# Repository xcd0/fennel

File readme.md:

# fennel
T
fan90のPCB、アクリルケースの発注が終わった。暇。この間に次のキーボードを作る。  
とりあえず名前はそのまま引き継ぐ。古いものは別ブランチに残す。別リポジトリにするかも...

## コンセプト

両手用左右分離型キーボード。fan90を小さくした。 片手に37キーの予定。  
ただしキーマトリクスが余る分を小さなリセットスイッチなどで設け、  
あまり使用頻度が高くない機能を割り当てる(マイコンの設定など)。  

* 指に合わせていい感じにキーが配置されてる両手で使えるキーボード欲しい。fan90二つはちょっと...
* fan90は流行に逆らったマキシマムな設計だったので、次は長いものに巻かれる小さ目な設計にする。
* 基盤はfan90と同じように両面対応する。
* fan90では筋力的にできなかった左右分割のキーボードにする。（左右間で通信する）
* ~~ケースはできれば3Dプリンターを使ってみる。~~ 基盤でケース作る方向にした。
* fan90のねじ数が少なくてちょっとたわむのでねじを増やす。
* Pro MicroではなくBluePillを使ってみる。

外形が難しい... \_(:3 」∠ )\_

## 設計

fan90に比べ、
* 左右分離(通信)
* BluePillを使う(ARM)
の2点により難易度が上昇している。
というか参考にできる情報がすくない。

現状回路がよくなさそうなので長い目で決めていく。

* UART半二重通信をする予定
	* 
	* 右手のbluepillはスキャンしてひたすら左手に送信するだけ
	* 左手は受け取って左手のスキャン情報と合わせてPCにUSB経由で送信
	* 通信用の信号線(回路図のdata)はpullupしつつ、GNDとツェナーダイオードでつなぐ。
* pullup抵抗を入れる
	* 10kΩが多いみたい。
	* 1.5kΩの抵抗が余ってるからこれでもいいかな...
	* wikipediaによるとバイポーラは1kΩ～4.7kΩ、CMOSでは220kΩ～1MΩらしい
	* データシートにweak pull-up equivalent resistorの記述があるので、  
	内蔵のプルアップ抵抗も使えるみたい。VINとVSSをつなぐと30～50kΩになるみたい。(43ページ)
* RX は入力端子なので保護抵抗を入れる。
	* これも1.5kΩでいいかな...
	* データシートにたしかに10kΩ書いてあるので10kΩにした方がよさそう
* 使ってないIOピンもVCCかGNDに10kΩ挟んでつなぐ
	* どっちでもいいみたい
	* これは外部でプルアップ/ダウンする必要があるみたい
	> All unused pins must be held at a fixed voltage, by using the I/O output mode, an external pull-up or pull-down resistor
* キーマトリクスに割り当てるピン配置を変える

* 異種面付けをしてみた
	
	* お値段 5枚製造
		* 異種面付けで基板製造の費用$93
		* 異種面付けしないで３枚頼んだ時の基板製造費$33
	* かすかに安いが、後加工が必要になるので、その点で普通に注文したほうよい。

### STM32F103について

調べて分かったことのメモ。間違っているかも。

* 内部回路の電源が分かれている。
	* VBAT はRTCとか用
		* ボタン電池とかをつないでRTCを維持できるみたい。
	* 1.8Vはコア回路用
	* VDDはデジタル回路用
	* VDDAはアナログ回路用

* リセットは3種類ある
	1. 電源を切る
	1. NRSTをGNDにつなぐ
	1. backup領域のみリセットする(そもそもbackup領域とは..)
		* BDRSTレジスタでリセット
		* VDDがONでリセット
		* VBATがONでリセット

* ピンについて
	* PA9がTx、PA10がRx。
	* PA15、PB3、PB4はJRAGデバッグに使われている(JTAGデバッグとは...)ので使おうとするとひと手間いる。
	* PB2はジャンパにつながっている。
	* PA11、PA12はUSB端子につながっている。
	* generic bootloader向け
		* bootloaderの種類はbluepillの実装に合わせる。generic_boot20_xxx.binのxxxはLEDのpinに合わせる。
			* 合わせることでDFUモードの状態をLEDで表示できる。
		* PA12はUSBリセットに使われているので、外部HWをつながない方がよい。
		* PC13はDFUの状態をLEDで表示するのに使われているので、外部HWをつながない方がよい。
		* PC14はNRSTに使われているので、外部HWをつながない方がよい。
			* PC14を3.3VにプルアップするとDFU永続モードになる？
			* DFU永続モードにできるなら有用なので専用回路を実装したい。
			* PC14をhigh→リセット→書き込み→PC14を開放→リセットの流れっぽい。

* 書き込みについて
	* USB経由での書き込みはタイミングよくリセットボタンを押す必要があるらしい。
		* 「Arduinoの書き込みを押した後0.5秒後くらいにボードのリセットを押す」らしい...

## リンク集

* 一番詳しかった  
ＤＥＫＯのアヤシいお部屋。 - STM32F103 https://ht-deko.com/arduino/stm32f103c8t6.html

* DFUモードの0.5秒の情報はここ  
adfmac/bluepill-arduino.md https://gist.github.com/tadfmac/f1dffc8c674ddaa8bd2340a8ddec65be

## ケース

基板と一緒に頼んだ。

## 回路間違っていた。
頼んだタイミングが残業で疲れた深夜だったため、いろいろミスった状態で発注した\_(:3 」∠ )\_
労働は体に良くない。

とりあえずゴリゴリ基盤を削って空中配線してごまかした。

## ファームウェア

[Ortho 75](https://github.com/qmk/qmk_firmware/tree/master/keyboards/cannonkeys/ortho75)を参考にする。

とりあえずこぴっていじる

<!--{{{-->

## 以下古いバージョン

<details>
<summary>v1 fan90 片手用フルキーボード</summary>

## one hand keyboard fan90

片手用キーボードです。G13のような用途を想定しています。  
左手で使うことを想定していますが、右手でも使えるようにPCBは作っています。  
流行りのミニマムなキーボードとは反対方向のマキシマムな方向のキーボードです。  
両手で使うことを想定していませんが、両面対応しているので2つ用意すれば可能です。  

初めての自作キーボードなので楽しみなのと不安なのが混在しています\_(:3 」∠ )\_
あくまで初めてつくる自作キーボードであるため、当然ながら動かない可能性が高いです。

<details>
<summary>開発経緯</summary>

### キーボード割ろうとしたら曲がった
* ありものは素晴らしい、でも自分で作ってみたい。よし、初めてのキーボード自作だ！PCBから作るぞ\\('ω')/
* 今使ってるhelixよい。でもErgodox的な縦のずれがあるキーボードもよさそう。そういうの作ろう...
* 左右分割型のキーボード良い。割りたい！でも左右の通信とかどうやってるんだろう...ちゃんと作れるかな...
* とりあえずキーを並べてみる。小指とか根元に近く配置しよう...
* 見た目汚いな...とりあえずきれいに並べてみるか...あれ、なんか曲がってきた...
* あれこれ片手でフルキーボードいけるんじゃ...

という感じでした\_(:3 」∠ )\_  
つまりキーボードを割ろうとしたが、  
筋力が足りなかったため（左右に分割したときの左右間の通信を電源(VCC,GND)と信号線の3本でどうやって通信してるのかわからなかったので）、  
割れずに曲がってしまった。  
次作るときは割りたい。  
名前は見た目がうちわのようになったため。  もちろん余った基板は重めの団扇として使うことができる。
鍋敷きにしてもよい。
</details>

<details>
<summary>構想</summary>

#### コンセプト
以下で東西南北を言うときは、左手で中指の方向を北とした場合の手のひらからの方向を指します。

* 片手でたくさんのキーを使える。
	* フルキーボード相当のキーを使えるものとする。
		* 現状6x15のマトリクスで87キーを配置。
		* 残り３キーはあまり使わない用途向けにリセットスイッチ部品で配置。

* 片手で使いやすい。
	* 指毎の特徴に合わせて配置する。  
		例えば
		* 親指はゲームのコントローラーで多用されるように本来非常に性能が良い。  
		しかしキーボードを使う上で親指を生かすのは難しい。  
		Twitterの投票によると親指に複数のキーを割り当てているときに使っているキーの数はせいぜい4キーらしい。  
		このキーボードでは多めに5キーを割り当てる。
		* 人差し指は性能が良くQWERTYでもほかの指より多いキーを担当する。  
		このキーボードでも人差し指の担当は多くする。
		* 中指は人差し指と同じくらいのせいのがある。中指にも多めのキーを割り当てる。
		* 薬指は中指と一緒に動かないと性能が良くないので、キーボードではあまり性能を発揮できない。
		ただし、北西方向は強く、北西方向に関しては小指より適している。。
		* 小指は短いので、北西方向の移動は難しい。  
		しかし西方向、南西方向はそこそこ性能が良い。
	* 指に合わせてキーを配置する。
		* 変則的な配置なので指１本に対して割り当てられたキーの数は様々。
			* 現状小指20、薬指15、中指12、人差し指31、親指5キー。人差し指と小指は無駄キーを含む。足しても90にはならない。
		* 将来的にはキーを立体的に配置するのもよいが、現状は平面に配置。
	* 指は伸ばした状態のほうが押しやすく、キーを押し分けやすい。
		* 指の根本に近いキーよりも指を伸ばしたときに押すキーのほうが押しやすい。
		* 指の根元に近いキーを減らし、指を伸ばしたときに押すキーを増やす。
	* レイヤーは極力つかわない。
		* シフトキーのように押しながら操作することは片手だと難しい。

* すべてのキーを常に使うキーにはせず、使う用途に合わせてカスタマイズできるよう、無駄にキーを配置する。

#### 実現方法

* 以下の2点からキーを扇状に配置する。
	* 小指の性能を発揮できるように小指のキーは手首側に寄せる。
	* 伸ばした状態で使える人差し指、中指のキーを増やす。
* 列方向には揃えず、行方向にはそろえる。
* 無駄にキーを小指の西側、人差し指の東側、すべての指の北側に配置する。つまり一回り大きくする。

#### 将来的にやりたいこと

* QMKを使わずに作る。(現状使う)
* C以外の言語で作る。(現状C言語)
* マイコンを複数種類使えるようにする。(現状むずかしい)
* raspberry pi zeroと画面を搭載して、それ単体でPCとして動作させ多機能にする。(現状ソケットのみ用意)
* ケースを3Dプリンターなどでつくる。
* キーを立体的に配置する。

</details>

### PCB設計

kicadを使って設計した。

回路は6x15のマトリクス。column方向からスキャンし、rowを検出する。  
column方向のスキャンは床に転がっていたSN74HC595を使う。  
シフトレジスタを使えば簡単にスキャンできそう。  
これで信号線数を15-5で10本減らせることになる。  
pro microはデジタルIOピンが14本、デジタルとしても使えるアナログIOピンが4本なので、
最大18本をデジタルIOとして使うことができる。
6本をrowのデジタル入力に、5本をシフトレジスタへのデジタル出力に、
2本をリセットスイッチに使用することにした。
配置は特にこだわりなく並べた。このせいで後々苦労するかもしれないがまあ初めてなので良しとする。

### アクリルケース設計

* ケースもとりあえずアクリルで作ることにした。
* ケースもDXFで入稿できるみたいなのでkicadでそのまま作った。
	* SVGでもよさそうだがそもそもSVGで線幅を狭くするとinkscapeやchromeで表示したとき線が描画されない問題があった。
* アクリルは[工房Emerge+](https://www.emergeplus.jp/laser-cutting-service/)を使ってみることにした。
	* elecrowはウェブサイトの調子が良くないのか、そもそもサービス中止中なのか、  
	https://twitter.com/xcd0/status/1233658167684296704  
	のようにfalseとなっていた。
	* 遊舎工房は、キーボードのサイズが大きいので元のアクリル板が最低でもA3より大きな必要があり、  
	A5,A4,450 X 300と、450x300以外の選択肢がなく、このサイズでも2枚発注する必要がある。  
	そして150x300程度の余白ができてしまう。
	* Emarge+は600x300に対応しており、これだと１枚に収まる。なのでここにしてみた。
	* 遊舎工房とEmerge+はillustratorありきの体制で、すごくストレスフルであった。
	* inkscapeは線幅の問題で使えず、外形と内形を色を変えるとかレイヤーを変えるとか言った操作はillustratorがないと難しいというか不可能な作業であった。
	* 今回５個ほどソフトを試したが、どれも満たせずあきらめてillustratorの7日間仕様版を使った。
	* 次回はaiやsvgではなくDXFで入稿したい。
	* elecrow復活してほしい...
* データ蹴られるかと思ったがとりあえず通った。
* DXFもレイヤー分けていればよいらしい。

### プログラム作成

qmkでもよいがとりあえず動作確認にarduinoを使う。
以下を参考にarduino studioで書き込めるか調べる。
https://learn.sparkfun.com/tutorials/pro-micro--fio-v3-hookup-guide#installing-windows
https://learn.sparkfun.com/tutorials/pro-micro--fio-v3-hookup-guide/hardware-overview-pro-micro

</details>
<!--}}}-->

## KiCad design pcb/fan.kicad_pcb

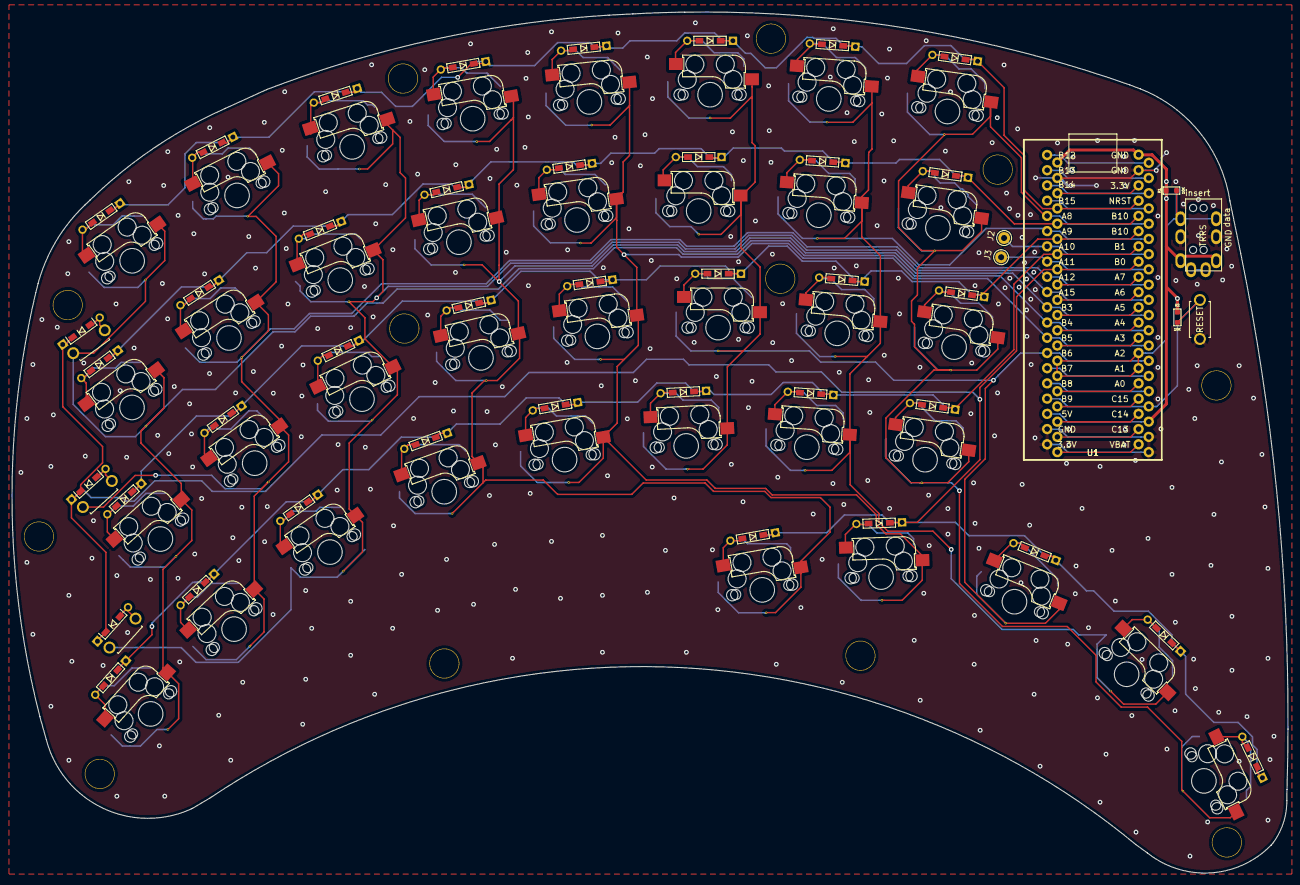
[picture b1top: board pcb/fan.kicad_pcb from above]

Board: 2 copper layers, 212.8 x 143.6 mm, 59 parts (0 on the bottom side), 19 nets.

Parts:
J1: MJ-4PP-9
J2, J3: Conn_01x01_Female; Pin_D1.0mm_L10.0mm
R1, R2: 10K; R_1608_rev2
Ref**: Val**; HOLE
Ref**#2, Ref**#3, Ref**#4, Ref**#5, Ref**#6, Ref**#7, Ref**#8, Ref**#9, Ref**#10, Ref**#11, Ref**#12: Val**; HOLE
SW1, SW2, SW3, SW4, SW6, SW7, SW8, SW9, SW11, SW12, SW13, SW14, SW16, SW17, SW18, SW19, SW20, SW21, SW22, SW23, SW24, SW25, SW26, SW27, SW28, SW29, SW30, SW31, SW32, SW33, SW34, SW35, SW36, SW37, SW38, SW39, SW40: SW_PUSH-kbd; CherryMX_MidHeight_Hotswap_edit
SW5, SW10, SW15: SW_PUSH-kbd; ResetSW_with_diode
SW41: SW_PUSH; ResetSW
U1: BluePill_STM32F103C; BluePill_STM32F103C_0.9_Double

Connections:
GND: J1.C, SW41.2, U1.19, U1.20, U1.39
unnamed: J2.1, U1.7
unnamed: J3.1, U1.8
Rx: J1.B, R1.2, U1.26, U1.27
VCC: J1.D, R1.1, R2.1, U1.18, U1.40
col00: SW1.1, SW2.1, SW3.1, SW4.1, SW5.1, U1.12
col01: SW6.1, SW7.1, SW8.1, SW9.1, SW10.1, U1.9
col02: SW11.1, SW12.1, SW13.1, SW14.1, SW15.1, U1.10
col03: SW16.1, SW17.1, SW18.1, SW19.1, SW20.1, U1.11
col04: SW21.1, SW22.1, SW23.1, SW24.1, SW25.1, U1.13
col05: SW26.1, SW27.1, SW28.1, SW29.1, SW30.1, U1.14
col06: SW31.1, SW32.1, SW33.1, SW34.1, SW35.1, U1.6
col07: SW36.1, SW37.1, SW38.1, SW39.1, SW40.1, U1.5
hardware_reset: R2.2, SW41.1, U1.17
row00: SW1.3, SW6.3, SW11.3, SW16.3, SW21.3, SW26.3, SW31.3, SW36.3, U1.37
row01: SW2.3, SW7.3, SW12.3, SW17.3, SW22.3, SW27.3, SW32.3, SW37.3, U1.36
row02: SW3.3, SW8.3, SW13.3, SW18.3, SW23.3, SW28.3, SW33.3, SW38.3, U1.35
row03: SW4.3, SW9.3, SW14.3, SW19.3, SW24.3, SW29.3, SW34.3, SW39.3, U1.34
row04: SW5.3, SW10.3, SW15.3, SW20.3, SW25.3, SW30.3, SW35.3, SW40.3, U1.33

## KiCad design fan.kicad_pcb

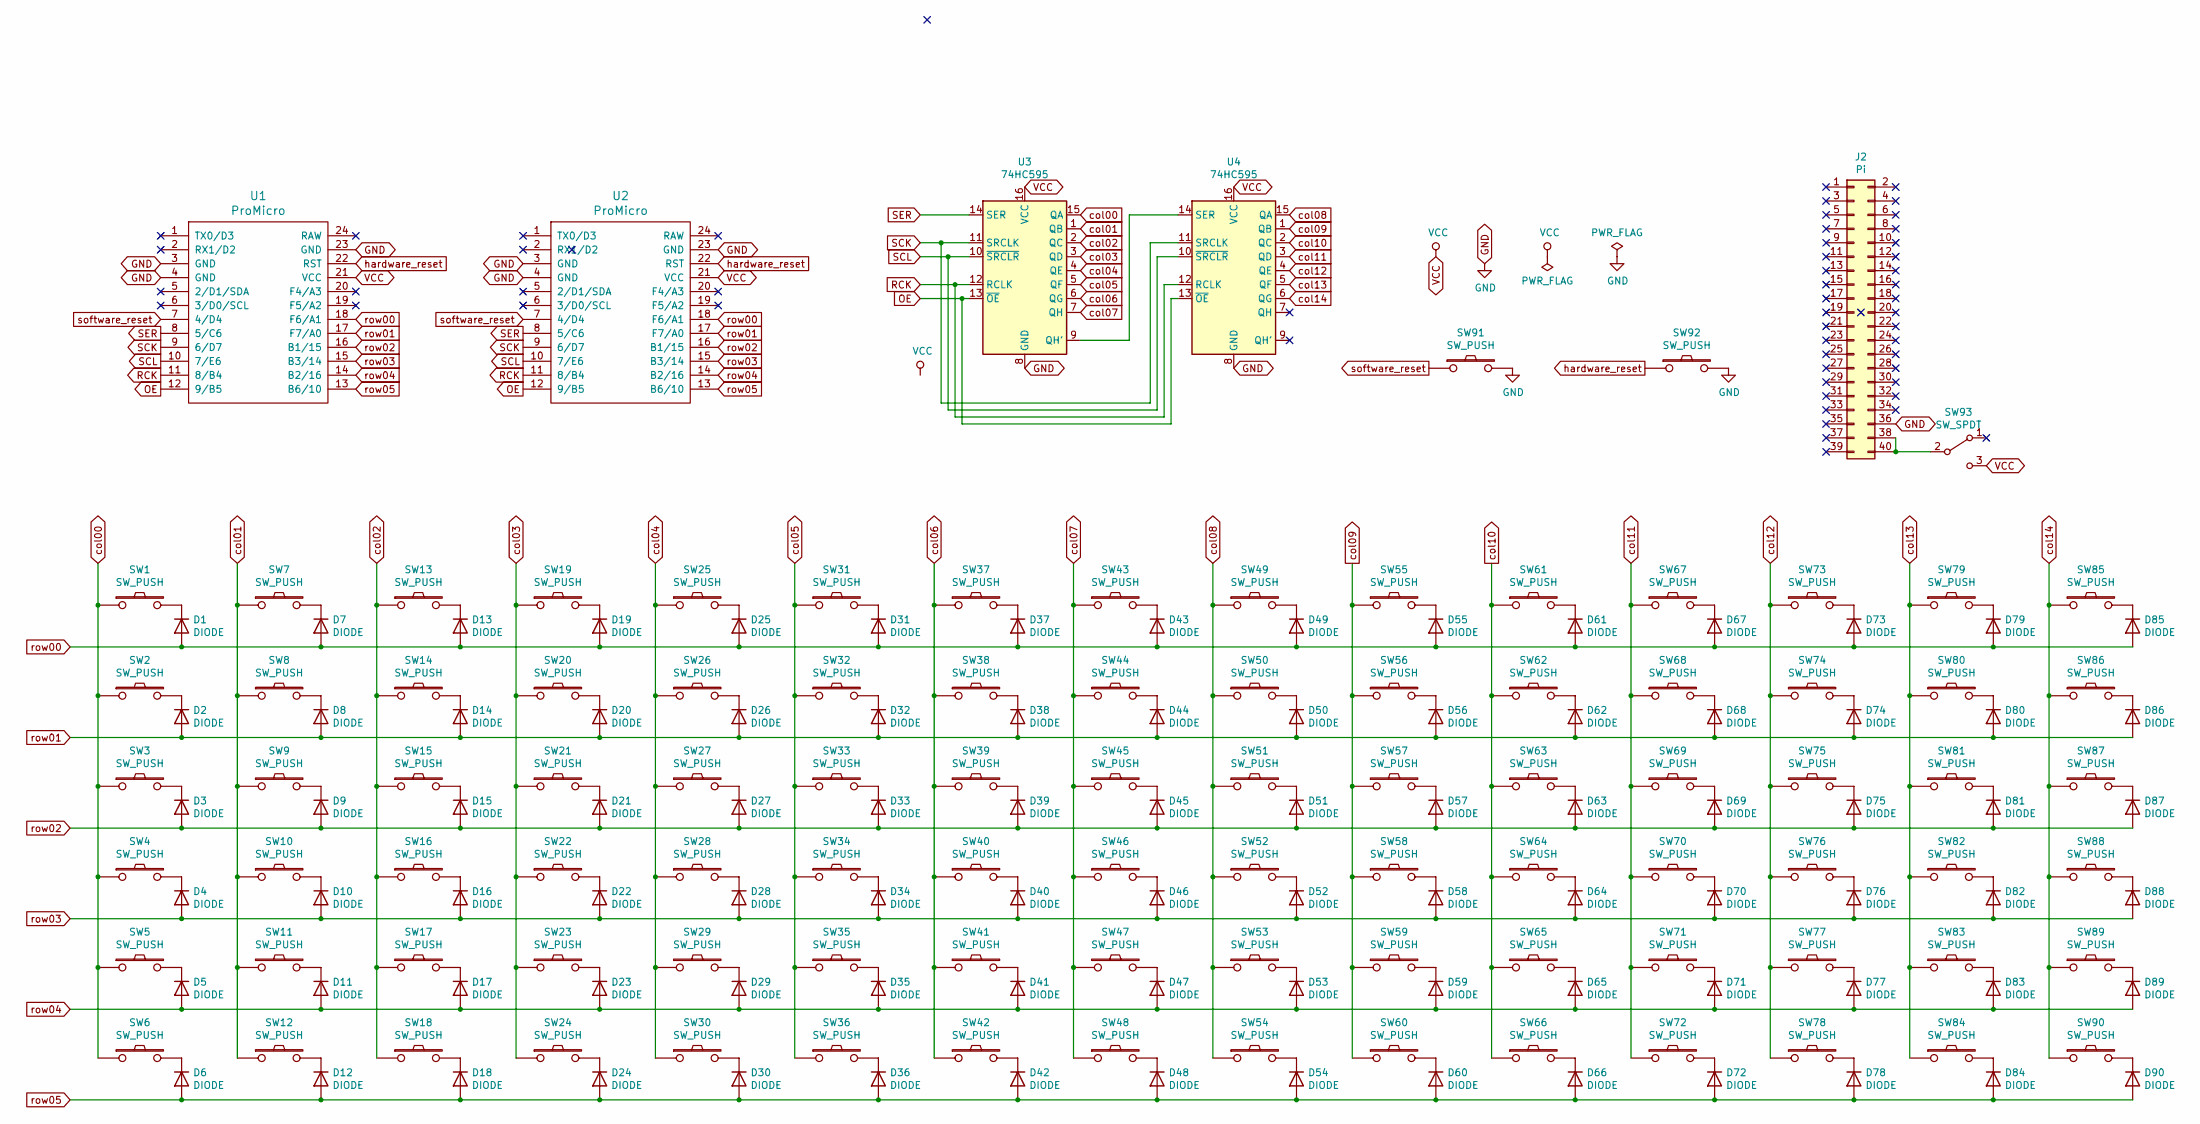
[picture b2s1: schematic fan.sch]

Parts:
D1, D2, D3, D4, D5, D6, D7, D8, D9, D10, D11, D12, D13, D14, D15, D16, D17, D18, D19, D20, D21, D22, D23, D24, D25, D26, D27, D28, D29, D30, D31, D32, D33, D34, D35, D36, D37, D38, D39, D40, D41, D42, D43, D44, D45, D46, D47, D48, D49, D50, D51, D52, D53, D54, D55, D56, D57, D58, D59, D60, D61, D62, D63, D64, D65, D66, D67, D68, D69, D70, D71, D72, D73, D74, D75, D76, D77, D78, D79, D80, D81, D82, D83, D84, D85, D86, D87, D88, D89, D90: DIODE; D3_TH_SMD
J2: Pi; PinSocket_2x20_P2.54mm_Vertical
SW1, SW2, SW3, SW4, SW5, SW6, SW7, SW8, SW9, SW10, SW11, SW12, SW13, SW14, SW15, SW16, SW17, SW18, SW19, SW20, SW21, SW22, SW23, SW24, SW25, SW26, SW27, SW28, SW29, SW30, SW31, SW32, SW33, SW34, SW35, SW36, SW37, SW38, SW39, SW40, SW41, SW42, SW43, SW44, SW45, SW46, SW47, SW48, SW51, SW52, SW53, SW54, SW56, SW57, SW58, SW59, SW60, SW61, SW62, SW63, SW64, SW65, SW66, SW67, SW68, SW69, SW70, SW71, SW72, SW73, SW74, SW75, SW76, SW77, SW78, SW79, SW80, SW81, SW82, SW83, SW84, SW85, SW86, SW87, SW88, SW89, SW90: SW_PUSH; CherryMX_Hotswap
SW49, SW50, SW55, SW91, SW92: SW_PUSH; ResetSW
SW93: SW_SPDT; SW_Slide_1P2T_CK_OS102011MS2Q
U1, U2: ProMicro; ProMicro_v3.5
U3, U4: 74HC595; DIP-16_W7.62mm

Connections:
GND: J2.36, SW91.2, SW92.2, U1.3 (GND), U1.4 (GND), U1.23 (GND), U2.3 (GND), U2.4 (GND), U2.23 (GND), U3.8 (GND), U4.8 (GND)
unnamed: D1.2 (K), SW1.2
unnamed: D2.2 (K), SW2.2
unnamed: D3.2 (K), SW3.2
unnamed: D4.2 (K), SW4.2
unnamed: D5.2 (K), SW5.2
unnamed: D6.2 (K), SW6.2
unnamed: D7.2 (K), SW7.2
unnamed: D8.2 (K), SW8.2
unnamed: D9.2 (K), SW9.2
unnamed: D10.2 (K), SW10.2
unnamed: D11.2 (K), SW11.2
unnamed: D12.2 (K), SW12.2
unnamed: D13.2 (K), SW13.2
unnamed: D14.2 (K), SW14.2
unnamed: D15.2 (K), SW15.2
unnamed: D16.2 (K), SW16.2
unnamed: D17.2 (K), SW17.2
unnamed: D18.2 (K), SW18.2
unnamed: D19.2 (K), SW19.2
unnamed: D20.2 (K), SW20.2
unnamed: D21.2 (K), SW21.2
unnamed: D22.2 (K), SW22.2
unnamed: D23.2 (K), SW23.2
unnamed: D24.2 (K), SW24.2
unnamed: D25.2 (K), SW25.2
unnamed: D26.2 (K), SW26.2
unnamed: D27.2 (K), SW27.2
unnamed: D28.2 (K), SW28.2
unnamed: D29.2 (K), SW29.2
unnamed: D30.2 (K), SW30.2
unnamed: D31.2 (K), SW31.2
unnamed: D32.2 (K), SW32.2
unnamed: D33.2 (K), SW33.2
unnamed: D34.2 (K), SW34.2
unnamed: D35.2 (K), SW35.2
unnamed: D36.2 (K), SW36.2
unnamed: D37.2 (K), SW37.2
unnamed: D38.2 (K), SW38.2
unnamed: D39.2 (K), SW39.2
unnamed: D40.2 (K), SW40.2
unnamed: D41.2 (K), SW41.2
unnamed: D42.2 (K), SW42.2
unnamed: D43.2 (K), SW43.2
unnamed: D44.2 (K), SW44.2
unnamed: D45.2 (K), SW45.2
unnamed: D46.2 (K), SW46.2
unnamed: D47.2 (K), SW47.2
unnamed: D48.2 (K), SW48.2
unnamed: D49.2 (K), SW49.2
unnamed: D50.2 (K), SW50.2
unnamed: D51.2 (K), SW51.2
unnamed: D52.2 (K), SW52.2
unnamed: D53.2 (K), SW53.2
unnamed: D54.2 (K), SW54.2
unnamed: D55.2 (K), SW55.2
unnamed: D56.2 (K), SW56.2
unnamed: D57.2 (K), SW57.2
unnamed: D58.2 (K), SW58.2
unnamed: D59.2 (K), SW59.2
unnamed: D60.2 (K), SW60.2
unnamed: D61.2 (K), SW61.2
unnamed: D62.2 (K), SW62.2
unnamed: D63.2 (K), SW63.2
unnamed: D64.2 (K), SW64.2
unnamed: D65.2 (K), SW65.2
unnamed: D66.2 (K), SW66.2
unnamed: D67.2 (K), SW67.2
unnamed: D68.2 (K), SW68.2
unnamed: D69.2 (K), SW69.2
unnamed: D70.2 (K), SW70.2
unnamed: D71.2 (K), SW71.2
unnamed: D72.2 (K), SW72.2
unnamed: D73.2 (K), SW73.2
unnamed: D74.2 (K), SW74.2
unnamed: D75.2 (K), SW75.2
unnamed: D76.2 (K), SW76.2
unnamed: D77.2 (K), SW77.2
unnamed: D78.2 (K), SW78.2
unnamed: D79.2 (K), SW79.2
unnamed: D80.2 (K), SW80.2
unnamed: D81.2 (K), SW81.2
unnamed: D82.2 (K), SW82.2
unnamed: D83.2 (K), SW83.2
unnamed: D84.2 (K), SW84.2
unnamed: D85.2 (K), SW85.2
unnamed: D86.2 (K), SW86.2
unnamed: D87.2 (K), SW87.2
unnamed: D88.2 (K), SW88.2
unnamed: D89.2 (K), SW89.2
unnamed: D90.2 (K), SW90.2
unnamed: J2.38, J2.40, SW93.2 (B)
unnamed: U3.9 (QH'), U4.14 (SER)
OE: U1.12 (9/B5), U2.12 (9/B5), U3.13 (~OE), U4.13 (~OE)
RCK: U1.11 (8/B4), U2.11 (8/B4), U3.12 (RCLK), U4.12 (RCLK)
SCK: U1.9 (6/D7), U2.9 (6/D7), U3.11 (SRCLK), U4.11 (SRCLK)
SCL: U1.10 (7/E6), U2.10 (7/E6), U3.10 (~SRCLR), U4.10 (~SRCLR)
SER: U1.8 (5/C6), U2.8 (5/C6), U3.14 (SER)
VCC: SW93.3 (C), U1.21 (VCC), U2.21 (VCC), U3.16 (VCC), U4.16 (VCC)
col00: SW1.1, SW2.1, SW3.1, SW4.1, SW5.1, SW6.1, U3.15 (QA)
col01: SW7.1, SW8.1, SW9.1, SW10.1, SW11.1, SW12.1, U3.1 (QB)
col02: SW13.1, SW14.1, SW15.1, SW16.1, SW17.1, SW18.1, U3.2 (QC)
col03: SW19.1, SW20.1, SW21.1, SW22.1, SW23.1, SW24.1, U3.3 (QD)
col04: SW25.1, SW26.1, SW27.1, SW28.1, SW29.1, SW30.1, U3.4 (QE)
col05: SW31.1, SW32.1, SW33.1, SW34.1, SW35.1, SW36.1, U3.5 (QF)
col06: SW37.1, SW38.1, SW39.1, SW40.1, SW41.1, SW42.1, U3.6 (QG)
col07: SW43.1, SW44.1, SW45.1, SW46.1, SW47.1, SW48.1, U3.7 (QH)
col08: SW49.1, SW50.1, SW51.1, SW52.1, SW53.1, SW54.1, U4.15 (QA)
col09: SW55.1, SW56.1, SW57.1, SW58.1, SW59.1, SW60.1, U4.1 (QB)
col10: SW61.1, SW62.1, SW63.1, SW64.1, SW65.1, SW66.1, U4.2 (QC)
col11: SW67.1, SW68.1, SW69.1, SW70.1, SW71.1, SW72.1, U4.3 (QD)
col12: SW73.1, SW74.1, SW75.1, SW76.1, SW77.1, SW78.1, U4.4 (QE)
col13: SW79.1, SW80.1, SW81.1, SW82.1, SW83.1, SW84.1, U4.5 (QF)
col14: SW85.1, SW86.1, SW87.1, SW88.1, SW89.1, SW90.1, U4.6 (QG)
hardware_reset: SW92.1, U1.22 (RST), U2.22 (RST)
row00: D1.1 (A), D7.1 (A), D13.1 (A), D19.1 (A), D25.1 (A), D31.1 (A), D37.1 (A), D43.1 (A), D49.1 (A), D55.1 (A), D61.1 (A), D67.1 (A), D73.1 (A), D79.1 (A), D85.1 (A), U1.18 (F6/A1), U2.18 (F6/A1)
row01: D2.1 (A), D8.1 (A), D14.1 (A), D20.1 (A), D26.1 (A), D32.1 (A), D38.1 (A), D44.1 (A), D50.1 (A), D56.1 (A), D62.1 (A), D68.1 (A), D74.1 (A), D80.1 (A), D86.1 (A), U1.17 (F7/A0), U2.17 (F7/A0)
row02: D3.1 (A), D9.1 (A), D15.1 (A), D21.1 (A), D27.1 (A), D33.1 (A), D39.1 (A), D45.1 (A), D51.1 (A), D57.1 (A), D63.1 (A), D69.1 (A), D75.1 (A), D81.1 (A), D87.1 (A), U1.16 (B1/15), U2.16 (B1/15)
row03: D4.1 (A), D10.1 (A), D16.1 (A), D22.1 (A), D28.1 (A), D34.1 (A), D40.1 (A), D46.1 (A), D52.1 (A), D58.1 (A), D64.1 (A), D70.1 (A), D76.1 (A), D82.1 (A), D88.1 (A), U1.15 (B3/14), U2.15 (B3/14)
row04: D5.1 (A), D11.1 (A), D17.1 (A), D23.1 (A), D29.1 (A), D35.1 (A), D41.1 (A), D47.1 (A), D53.1 (A), D59.1 (A), D65.1 (A), D71.1 (A), D77.1 (A), D83.1 (A), D89.1 (A), U1.14 (B2/16), U2.14 (B2/16)
row05: D6.1 (A), D12.1 (A), D18.1 (A), D24.1 (A), D30.1 (A), D36.1 (A), D42.1 (A), D48.1 (A), D54.1 (A), D60.1 (A), D66.1 (A), D72.1 (A), D78.1 (A), D84.1 (A), D90.1 (A), U1.13 (B6/10), U2.13 (B6/10)
software_reset: SW91.1, U1.7 (4/D4), U2.7 (4/D4)

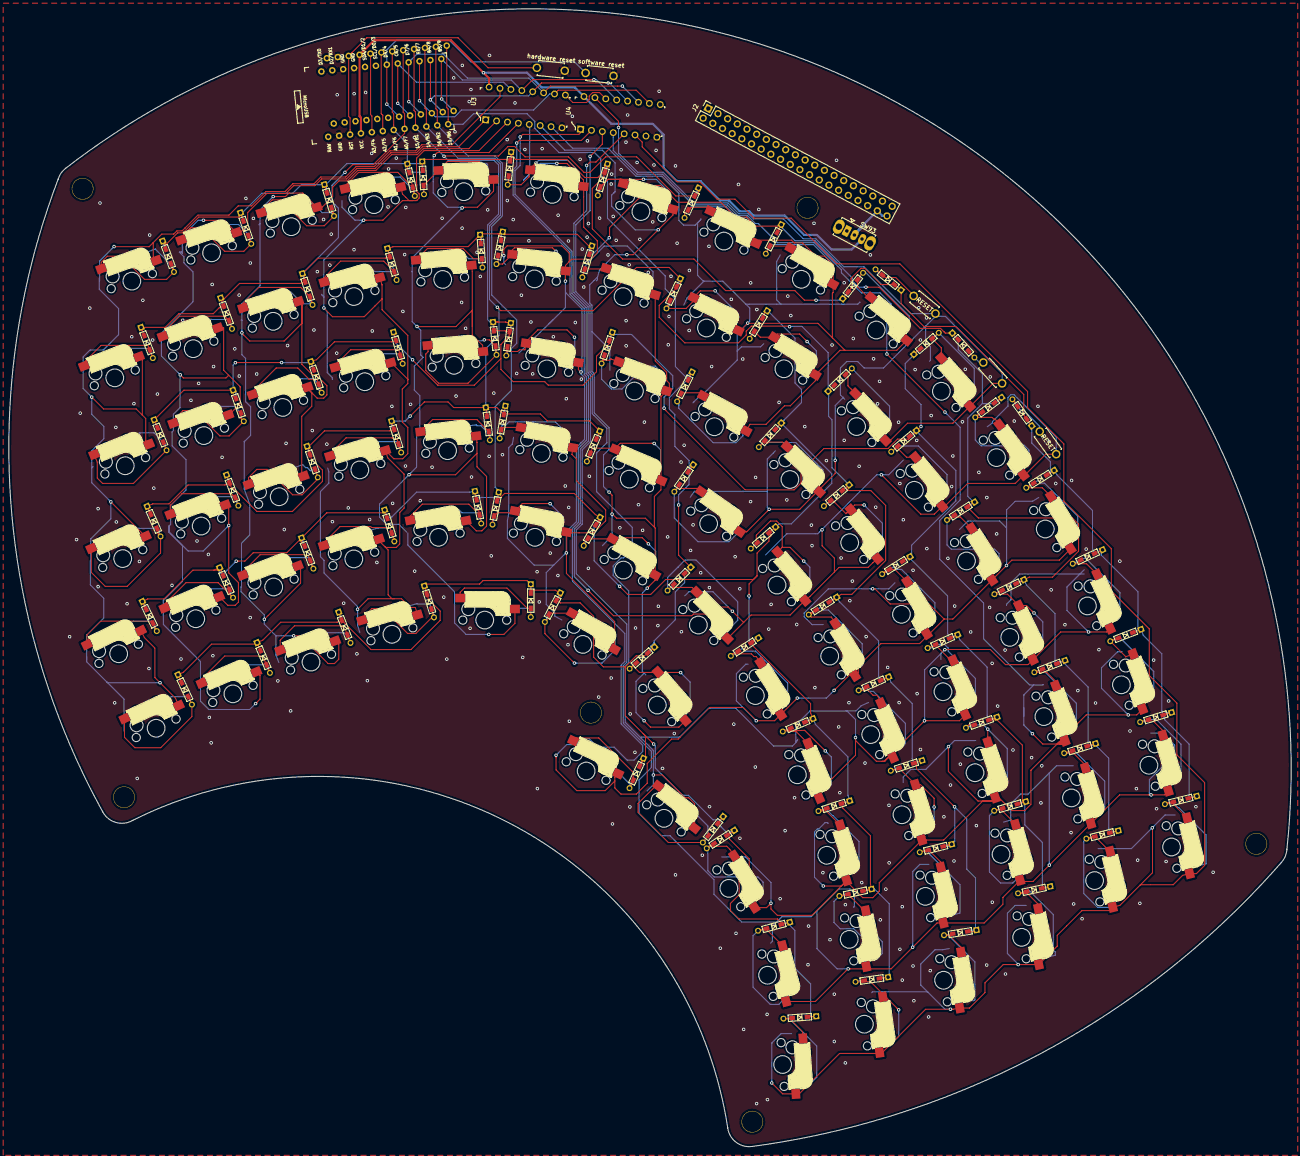
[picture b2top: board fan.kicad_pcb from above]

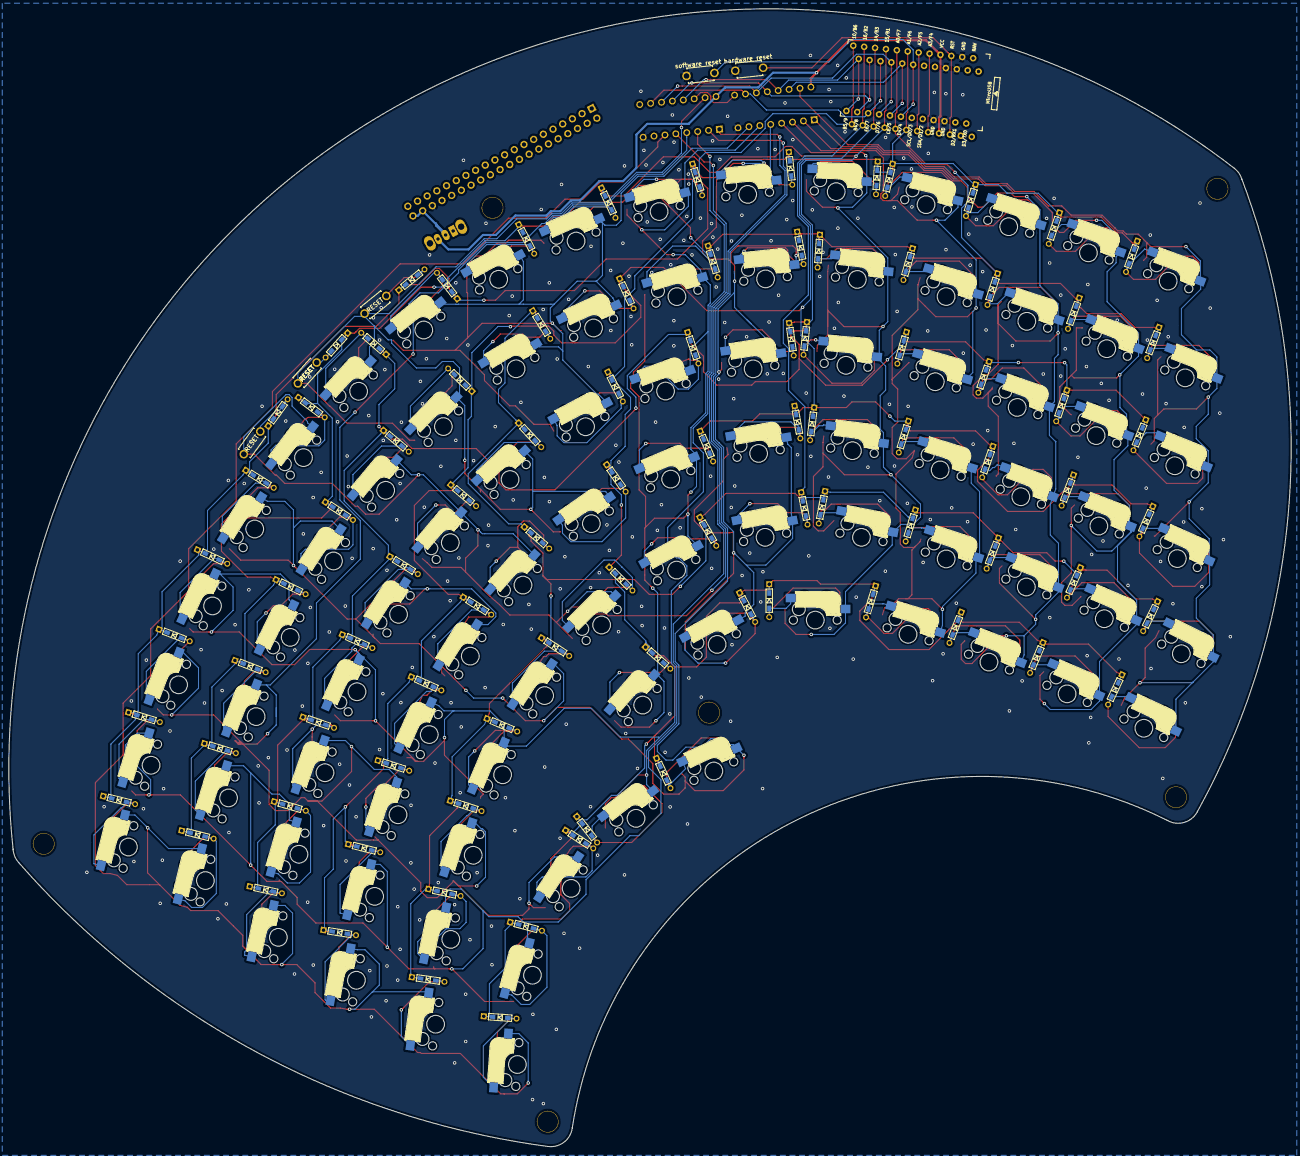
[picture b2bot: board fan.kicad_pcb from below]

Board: 2 copper layers, 297.2 x 263.7 mm, 194 parts (91 on the bottom side), 122 nets.

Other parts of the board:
Ref**: Val**; HOLE
Ref**#2, Ref**#3, Ref**#4, Ref**#5, Ref**#6: Val**; HOLE

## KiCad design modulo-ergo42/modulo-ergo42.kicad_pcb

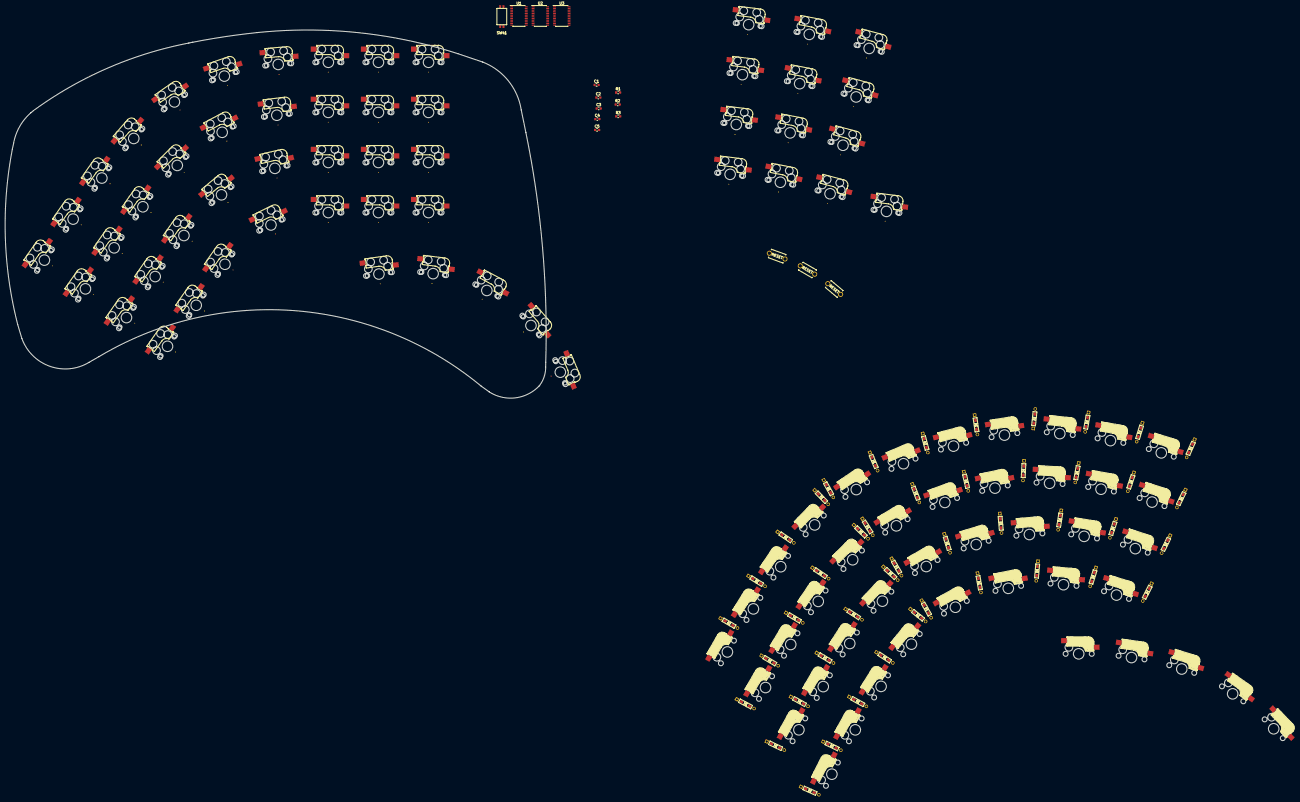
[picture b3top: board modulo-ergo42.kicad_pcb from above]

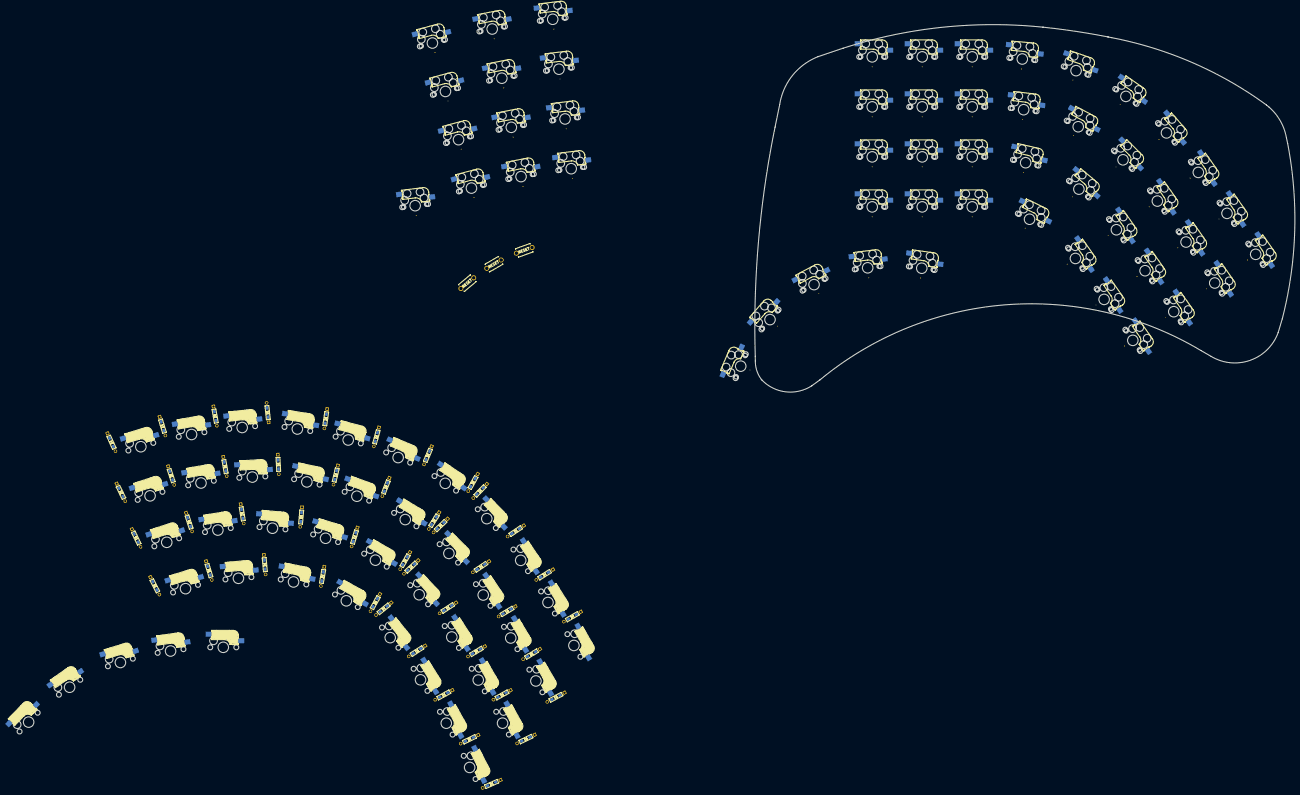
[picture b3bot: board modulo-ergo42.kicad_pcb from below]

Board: 2 copper layers, 210.6 x 143.3 mm, 155 parts (45 on the bottom side), 47 nets, no tracks yet.

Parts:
C1, C2, C5: 100 nF; C_0603_1608Metric
C3, C4: 1 uF; C_0603_1608Metric
D3, D4, D5, D8, D9, D10, D11, D14, D15, D16, D17, D20, D21, D22, D23, D26, D27, D28, D29, D32, D33, D34, D35, D38, D39, D40, D41, D46, D47, D48, D52, D53, D54, D57, D58, D59, D60, D62, D63, D64, D65, D68, D69, D70, D71: DIODE; D3_TH_SMD
R1: 10 kΩ; R_0603_1608Metric
R2, R3: 1 MΩ; R_0603_1608Metric
SW1, SW1#2, SW2, SW2#2, SW3, SW3#2, SW4, SW4#2, SW5, SW6, SW7, SW7#2, SW8, SW8#2, SW8#3, SW8#5, SW9, SW9#3, SW10#2, SW11#2, SW12, SW13, SW13#2, SW13#3, SW13#4, SW14, SW14#2, SW14#3, SW14#5, SW15#2, SW16#2, SW17#2, SW18, SW19, SW20#2, SW21#2, SW22#2, SW23#2, SW24, SW25, SW26#2, SW27#2, SW28#2, SW29#2, SW31, SW32#2, SW33#2, SW34#2, SW36, SW37, SW38#2, SW39#2: SW_Push; CherryMX_MidHeight_Hotswap_edit_without_diode
SW8#4, SW9#2, SW10, SW11, SW14#4, SW15, SW16, SW17, SW20, SW21, SW22, SW23, SW26, SW27, SW28, SW29, SW32, SW33, SW34, SW35, SW38, SW39, SW40, SW41, SW46, SW47, SW48, SW52, SW53, SW54, SW57, SW58, SW59, SW60, SW62, SW63, SW64, SW65, SW66, SW72, SW78, SW84, SW90: SW_PUSH; CherryMX_Hotswap
SW30, SW35#2, SW40#2: SW_Push; ResetSW
SW41#2: SW_DIP_x02; DipSwitch
U1, U2, U3: TCA9555PWR; TSSOP-24_4.4x7.8mm_P0.65mm

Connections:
3V3: C1.1, C2.1, C3.1, C4.1, C5.1, R1.1, R2.2, R3.1, U1.24, U2.21, U2.24, U3.21, U3.24
A1: R2.1, SW41#2.2, U1.2, U2.2, U3.2
A2: R3.2, SW41#2.1, U1.3, U2.3, U3.3
GND: C1.2, C2.2, C3.2, C4.2, C5.2, SW1#2.1, SW2#2.1, SW3#2.1, SW4#2.1, SW5.1, SW6.1, SW7#2.1, SW8#5.1, SW9#3.1, SW10#2.1, SW11#2.1, SW12.1, SW13#4.1, SW14#5.1, SW15#2.1, SW16#2.1, SW17#2.1, SW18.1, SW19.1, SW20#2.1, SW21#2.1, SW22#2.1, SW23#2.1, SW24.1, SW25.1, SW26#2.1, SW27#2.1, SW28#2.1, SW29#2.1, SW30.1, SW31.1, SW32#2.1, SW33#2.1, SW34#2.1, SW35#2.1, SW36.1, SW37.1, SW38#2.1, SW39#2.1, SW40#2.1, SW41#2.3, SW41#2.4, U1.12, U1.21, U2.12, U3.12
INT: R1.2, U1.1, U2.1, U3.1
R1C1: SW1#2.2, U1.4
R1C2: SW6.2, U1.5
R1C3: SW11#2.2, U1.6
R1C4: SW16#2.2, U1.7
R1C5: SW21#2.2, U1.8
R1C6: SW26#2.2, U1.9
R1C7: SW31.2, U1.10
R1C8: SW36.2, U1.11
R2C1: SW2#2.2, U1.20
R2C2: SW7#2.2, U1.19
R2C3: SW12.2, U1.18
R2C4: SW17#2.2, U1.17
R2C5: SW22#2.2, U1.16
R2C6: SW27#2.2, U1.15
R2C7: SW32#2.2, U1.14
R2C8: SW37.2, U1.13
R3C1: SW3#2.2, U2.4
R3C2: SW8#5.2, U2.5
R3C3: SW13#4.2, U2.6
R3C4: SW18.2, U2.7
R3C5: SW23#2.2, U2.8
R3C6: SW28#2.2, U2.9
R3C7: SW33#2.2, U2.10
R3C8: SW38#2.2, U2.11
R4C1: SW4#2.2, U2.20
R4C2: SW9#3.2, U2.19
R4C3: SW14#5.2, U2.18
R4C4: SW19.2, U2.17
R4C5: SW24.2, U2.16
R4C6: SW29#2.2, U2.15
R4C7: SW34#2.2, U2.14
R4C8: SW39#2.2, U2.13
R5C1: SW5.2, U3.4
R5C2: SW10#2.2, U3.5
R5C3: SW15#2.2, U3.6
R5C4: SW20#2.2, U3.7
R5C5: SW25.2, U3.8
R5C6: SW30.2, U3.9
R5C7: SW35#2.2, U3.10
R5C8: SW40#2.2, U3.11
SCL: U1.22, U2.22, U3.22
SDA: U1.23, U2.23, U3.23

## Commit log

2020-02-25 pro microに変更
2020-02-26 SN74HC595の両面対応
2020-02-26 大幅に手戻り 配線最初から
2020-02-27 再度配線しなおした
2020-02-27 寸法明記 272.00 x 295.00
2020-02-27 v1.2
2020-02-27 v1.21
2020-02-27 アクリルプレート用svgを出力
2020-02-27 全体の画像をsvgで出力
2020-02-27 add pdf
2020-02-27 発注した
2020-02-28 ケースを別ファイルに分けた
2020-02-28 アクリルパーツをフットプリントにしている最中 あと一つ大きなフタのみ
2020-02-28 フットプリントを更新
2020-02-29 アクリルレーザーカット用ファイルを追加
2020-03-01 アクリルカットサービスに見積もり出した
2020-03-01 QCADを使うとDXFのレイヤー、線色指定ができた、線幅は0.001にする方法が不明
2020-03-02 印刷用svgを出力してみた
2020-03-02 発注したアクリルケースの設計を元の基盤のファイルに含めたので古いファイルを削除
2020-03-04 v2.0 外形考え中
2020-03-04 迷走中...元にもどす
2020-03-04 基盤の外形を決定した
2020-03-08 v2.0 fan90を受けて修正。これでpro micro用の回路は官僚とする。(ケースはまだない)
2020-03-08 fan74をbluepillに変更
2020-03-08 readme.md の修正
2020-03-10 配線にちょっと詰まったのでやり直す
2020-03-12 fan74のPCBが一応完成した
2020-03-12 add datasheet
2020-03-14 fan74のケースを作成
2020-03-14 異種面付けしてみた がしないで3枚注文してもトントンだったので 普通に発注する予定
2020-03-15 天板 底板を作成 したものの、あと数ミリ小さくする予定
2020-03-15 fan90のプログラムを書いてみる前にfan74を保存
2020-03-16 JLPCBに注文してみた 安い
2020-03-25 キーマップを作った うごかない たいへん
2020-03-28 clean
2020-03-28 update ortho75
2020-03-28 とりあえず使ってないピンを割り当ててピン数をそろえてみた しかし変わらなかった
2020-03-28 PRODUCT_IDを変えてみた 変わらずエラー
2020-03-28 ピン数が合わせられてなかった 1つ足したらうまくいった
2020-03-28 正しく認識されるようにはなった 入力はできない
2020-03-29 Dupdate
